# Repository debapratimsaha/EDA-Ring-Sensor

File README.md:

# EDA Sensor Board 
This repository is an initial prototype of a low-cost [Electrodermal Activity](https://en.wikipedia.org/wiki/Electrodermal_activity) Sensor that I was working on in early 2014. This sensor measures electrodermal activity at the index and middle fingers and this current prototype is in a ring form-factor. 

### Circuit Description
The circuit is a resistor divider connected to a Texas Instruments INA337 instrument amplifier. The output is passed through an anti-aliasing filter before being read by the 10-bit ADC in an atTiny85 micro. 

### Firmware Description
The firmware is modelled as a state-machine which reads the ADC values, maps the average of 1s of data bytes into some coloring ranges and then controls an RGB-LED in real-time. The implemented state-machine is:

The video below shows the LED going through different phases of operation while the human is going through Forced Maximal Inhalation:

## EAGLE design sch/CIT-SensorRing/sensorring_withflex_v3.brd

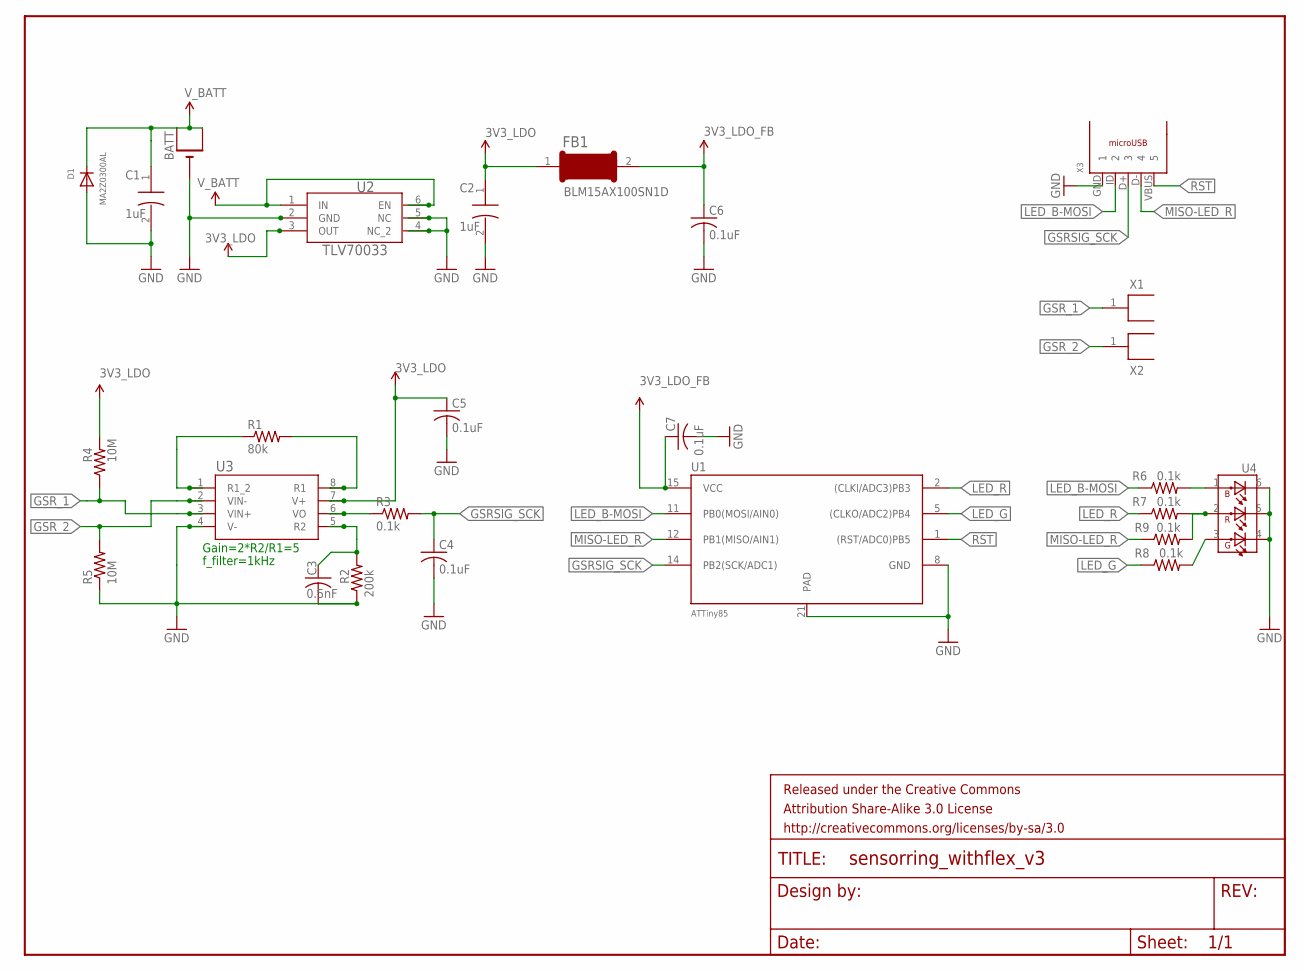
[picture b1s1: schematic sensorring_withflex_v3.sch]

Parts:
BATT: CR2032SMT; CR2032-SMD
C1, C2: 1uF; C1005; MPN C1005X5R0J105M050BB
C3: 0.5nF; C0402
C4, C5, C6, C7: 0.1uF; C0402; MPN C1005X5R1H104K050BB
D1: MA2Z0300AL; SOD-323F
FB1: BLM15AX100SN1D; 0402
FRAME1: FRAME-LETTER; CREATIVE_COMMONS
R1: 80k; R0402; MPN CRCW040240K2FKED
R2: 200k; R0402; MPN CRCW0402200KFKED
R3, R6, R7, R8: 0.1k; R0402; MPN CH0402-100RGF
R4, R5: 10M; R0402; MPN CRCW04021M00FKED
R9: 0.1k; R0402
U1: ATTiny85; 20M1; MPN ATTINY84-15MZ
U2: TLV70033; DSE6; MPN TLV70033DSET
U3: INA337_DGK_8; DGK8
U4: PICOLED-RGB-1MMX1MM5; PICOLED-1MM_1MM5
X1, X2: GSR_FLEX; GSR_FLEX_LEAD
X3: USB-MICRO-B; USB-MICROB

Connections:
3V3_LDO: C2.1, C5.1, FB1.1, R4.2, U2.3 (OUT), U3.7 (V+)
3V3_LDO_FB: C6.1, C7.1, FB1.2, U1.15 (VCC)
GND: BATT.-, C1.2, C2.2, C3.2, C4.2, C5.2, C6.2, C7.2, D1.A, R2.1, R5.1, U1.8 (GND), U1.21 (PAD), U2.2 (GND), U2.4 (NC_2), U2.5 (NC), U3.4 (V-), U4.4 (A_G), U4.5 (A_R), U4.6 (A_B), X3.GND (1)
GSRSIG_SCK: C4.1, R3.2, U1.14 (PB2(SCK/ADC1)), X3.D+ (3)
GSR_1: R4.1, U3.3 (VIN+), X1.1
GSR_2: R5.2, U3.2 (VIN-), X2.1
LED_B-MOSI: R6.1, U1.11 (PB0(MOSI/AIN0)), X3.ID (2)
LED_G: R8.1, U1.5 ((CLKO/ADC2)PB4)
LED_R: R7.1, U1.2 ((CLKI/ADC3)PB3)
MISO-LED_R: R9.1, U1.12 (PB1(MISO/AIN1)), X3.D- (4)
unnamed: R3.1, U3.6 (VO)
unnamed: R6.2, U4.1 (C_B)
unnamed: R1.2, U3.8 (R1)
unnamed: R1.1, U3.1 (R1_2)
unnamed: R8.2, U4.3 (C_G)
unnamed: C3.1, R2.2, U3.5 (R2)
unnamed: R7.2, R9.2, U4.2 (C_R)
RST: U1.1 ((RST/ADC0)PB5), X3.VBUS (5)
V_BATT: BATT.+$1 (+), BATT.+$2 (+1), C1.1, D1.C, U2.1 (IN), U2.6 (EN)

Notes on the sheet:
Gain=2*R2/R1=5
f_filter=1kHz

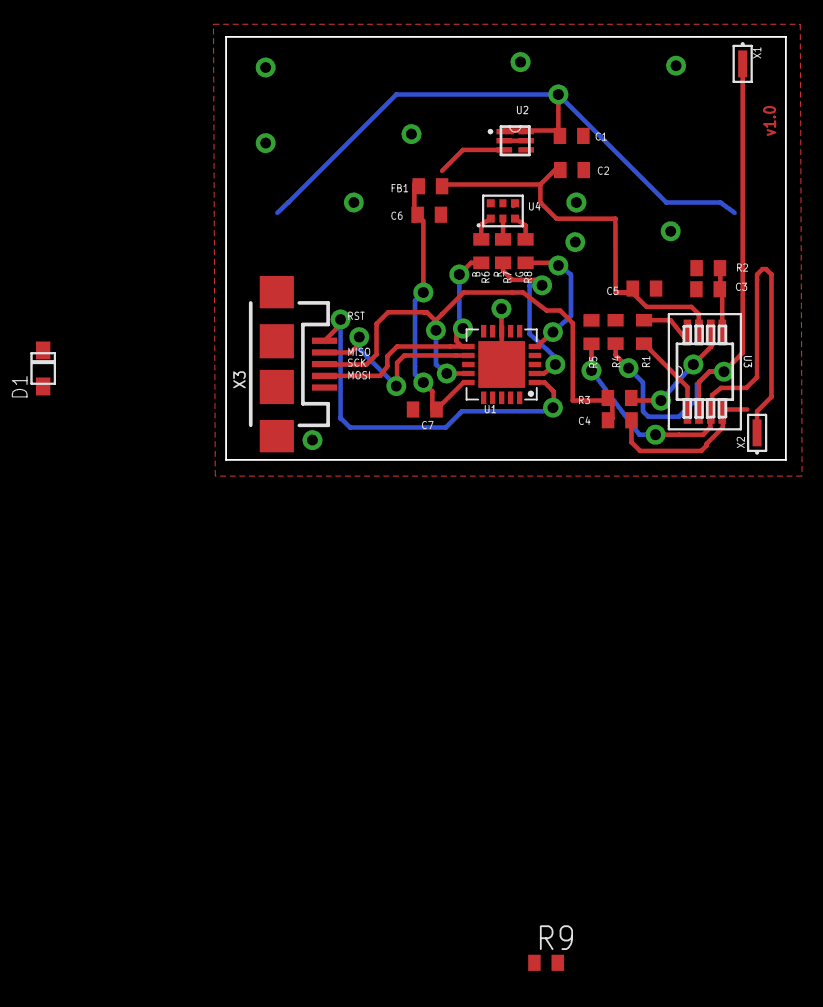
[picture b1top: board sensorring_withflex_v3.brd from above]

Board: 2 copper layers, 31.1 x 23.5 mm, 27 parts (1 on the bottom side), 19 nets.

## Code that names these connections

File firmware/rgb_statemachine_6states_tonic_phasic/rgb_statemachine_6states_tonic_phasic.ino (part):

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SoftwareSerial mySerial(rxPin, txPin);
#else
// Define the LED Pins    
#define LED_R    3              // Pin 3 -- Red LED
#define LED_G    4              // Pin 4 -- Green LED
#endif
#define LED_B    0              // Pin 0 -- Blue LED

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#if DEBUG_MODE  
  mySerial.begin(9600);  
#else
  pinMode(LED_R, OUTPUT);     
  pulse (LED_R,2);
  pinMode(LED_G, OUTPUT);     
  pulse (LED_G,2);
#endif  
  pinMode(LED_B, OUTPUT);     
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    /*
    Port B Data Direction Register (controls the mode of all pins within port B)
    DDRB is 8 bits: [unused:unused:DDB5:DDB4:DDB3:DDB2:DDB1:DDB0]
    1<<DDB4: sets bit DDB4 (data-direction, port B, pin 4), which puts PB4 (port B, pin 4) in output mode
    1<<DDB1: sets bit DDB1 (data-direction, port B, pin 1), which puts PB1 (port B, pin 1) in output mode
    1<<DDB0: sets bit DDB0 (data-direction, port B, pin 0), which puts PB0 (port B, pin 0) in output mode
    */
//    DDRB = 1<<DDB4 | 1<<DDB1 | 1<<DDB0;

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
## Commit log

2017-08-18 EDA Sensor board 1v0
    This commit implements:
    * 1sec update freq for SCL and remapping of LED coloring zone
    * LED color map (see description)
2017-08-18 Edited image url
2017-08-18 Updated video thumbnail
2017-08-24 Changed readme

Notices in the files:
parts and their libraries:
SparkFun-Aesthetics: Licensing: CC v3.0 Share-Alike You are welcome to use this library for commercial purposes.
SparkFun-Aesthetics: Released under the Creative Commons Attribution Share-Alike 3.0 License
SparkFun-Aesthetics: http://creativecommons.org/licenses/by-sa/3.0
